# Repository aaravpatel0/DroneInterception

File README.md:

# DroneDetection

This is my drone tracking and turret project. The main goal was to detect a drone with a camera, estimate where it is in 3D space, and move a pan/tilt turret so the camera stays pointed at it.

I am Aarav Patel. I started this project as a computer vision turret, but it turned into a bigger system while I was building it. I worked on the YOLO detector, the live tracker, the Pico turret firmware, the CAD, and two custom PCBs. I also tried controlling a small commercial drone through its controller, but that got messy, so I moved toward custom electronics for the drone frame instead.

The project is not a finished product. It is a working prototype and a record of what I built, tested, changed, and still need to finish.

## Current Status

- The YOLOv8 drone detector works.
- The live camera tracker works.
- The tracker estimates the drone position relative to the camera.
- The tracker predicts short-term movement so the turret does not only react to the last frame.
- The Pico 2 turret controller moves pan with a stepper motor and tilt with a servo.
- Stepper acceleration ramping is in the firmware so the motor stalls less.
- The turret has been tested with live tracking and depth estimates.
- The drone PCB and turret PCB are designed and have fabrication files.
- The next hardware step is assembling and testing the manufactured boards.

## Project Photos

## Demo Links

| Demo | What it shows | Repo file | Drive link |
| --- | --- | --- | --- |
| YouTube project demo | Main video for the project | - | [Watch on YouTube](https://youtu.be/fUEFKIeKq6E?si=KoJLhP0QhyuUc3A9) |
| Live turret tracking | The physical turret tracking a detected drone | - | [Drone Tracking Turret.mp4](https://drive.google.com/file/d/1UBQOuaAiReNZodWpAV6A1nRXlFVHGqKZ/view?usp=drivesdk) |
| Detection proof of concept | Camera detection and tracking test | - | [Proof of Concept - Drone Tracked.mp4](https://drive.google.com/file/d/1Y8ixHSbWaxlFa2D4qZv8LF1yn2z77p-x/view?usp=drivesdk) |
| Fast follow simulation | Simulated drone following a target | [MP4](assets/demo_simulations/follow_tracking_demo.mp4) / [GIF](assets/demo_simulations/follow_tracking_demo.gif) | [Drive MP4](https://drive.google.com/file/d/1x22EfQROl3rcCMJz3o-rANU-yGck9Fjs/view?usp=drivesdk) / [Drive GIF](https://drive.google.com/file/d/1ceiqXWkpfdoIr6vI1aE4kro-Gwh2Y9jS/view?usp=drivesdk) |
| Orbit simulation | Simulated drone orbiting around the target | [MP4](assets/demo_simulations/orbit_tracking_demo.mp4) / [GIF](assets/demo_simulations/orbit_tracking_demo.gif) | [Drive MP4](https://drive.google.com/file/d/1vTIU1h2euXmmVWb8Ut7vwJZywcUVn1Vr/view?usp=drivesdk) / [Drive GIF](https://drive.google.com/file/d/1toew0ILT582uKQxMksciPWsyv_LBWJpW/view?usp=drivesdk) |
| Safe standoff simulation | Simulated follow behavior that keeps distance | [MP4](assets/demo_simulations/standoff_tracking_demo.mp4) / [GIF](assets/demo_simulations/standoff_tracking_demo.gif) | [Drive MP4](https://drive.google.com/file/d/1BEXhN5-Scd0X3nanZK4e2Cr_hdrNLuV4/view?usp=drivesdk) / [Drive GIF](https://drive.google.com/file/d/1r3fI6IdqFA_aWafnw3gRHlx3CpV9DbdE/view?usp=drivesdk) |
| Full ship folder | Videos, previews, and extra files | - | [Google Drive folder](https://drive.google.com/drive/folders/1Nn7UfG2TgwVNnhRaEpTsOkTEUmSowxKg) |

The simulation files are here:

- [drone_detector/live_tracker/demo_flight_simulations.ipynb](drone_detector/live_tracker/demo_flight_simulations.ipynb)
- [drone_detector/live_tracker/demo_flight_simulations.py](drone_detector/live_tracker/demo_flight_simulations.py)

To regenerate the simulation clips:

```powershell
cd C:\Users\aptcs\Downloads\Projects\DroneDetection
.\drone_detector\.venv\Scripts\python.exe .\drone_detector\live_tracker\demo_flight_simulations.py --scenario all
```

## CAD

I made the turret CAD in Onshape:

[Open the turret CAD in Onshape](https://cad.onshape.com/documents/1e954f2e6fb0afe0e50c1e47/w/2cc3740a39c70e9d1274ecfc/e/ad41d11dd19aaeac7b789fd0?renderMode=0&uiState=6a3ad88aa638e38f0ba9bea5)

## Project Layout

```text
DroneDetection/
|-- README.md
|-- JOURNAL.md
|-- assets/
|   |-- demo_simulations/          # rendered simulation videos and GIFs
|   `-- project_photos/            # photos, screenshots, and PCB previews
|-- Drone PCB/                     # drone-frame board KiCad files, Gerbers, and STEP
|-- Turret Control PCB/            # turret controller KiCad files, Gerbers, and STEP
|-- drone_detector/
|   |-- live_tracker/              # camera tracking, 3D position, prediction, turret control
|   |-- pico_turret_platformio/    # Pico 2 turret firmware
|   |-- pico_drone_platformio/     # Pico 2 drone-control firmware
|   |-- pico_drone_controller/     # older MicroPython drone-control prototype
|   |-- esp32_drone_bridge/        # ESP32-C3 and BMI160 test work
|   |-- scripts/                   # Docker and workflow helper scripts
|   |-- train_yolov8.py
|   |-- evaluate_model.py
|   `-- run_tracker_sim.ps1
|-- dataset_toolkit/               # dataset scripts and reports
`-- archived/                      # older files I kept for reference
```

## Hardware

### Turret

The turret uses:

- USB camera for video input.
- Raspberry Pi Pico 2 for the turret controller.
- Stepper driver and NEMA 17 stepper for pan.
- Servo for tilt.
- 12V input power.
- 12V-to-8.4V buck/BEC for the servo rail on the turret PCB.
- Custom turret controller PCB to replace the breadboard wiring.

### Drone Frame

I first tried controlling the drone by sending filtered voltage signals into the original controller. It kind of worked, but it was not clean enough. The original joystick circuit kept affecting the voltages, and I did not want the final version to depend on a hacked controller.

After that, I designed a custom board for the small SP350-style drone frame. The board is meant to reuse the frame, motors, and propellers, but make the electronics easier to understand and modify.

The drone PCB includes:

- A compact shape for the reused frame.
- Four brushed motor outputs.
- Pads for motor and battery wires.
- Shared ground and cleaner power routing.
- Space to keep working on offboard control electronics.

## How It Works

### 1. Dataset And Training

I used YOLO-format drone datasets and merged them into one dataset with one class: `drone`. The scripts can merge datasets, clean labels, preview annotations, train the model, and evaluate it.

Main scripts:

- `drone_detector/merge_roboflow_datasets.py`
- `drone_detector/clean_dataset.py`
- `drone_detector/preview_labels.py`
- `drone_detector/train_yolov8.py`
- `drone_detector/evaluate_model.py`

The tracker looks for this model first:

```text
drone_detector/models/production_drone_model.pt
```

If it is not there, it tries this one:

```text
drone_detector/models/drone_roboflow_best.pt
```

### 2. Detection

`drone_detector/live_tracker/turret_tracker.py` reads camera frames and runs YOLOv8. It picks the best drone box, finds the center of that box, and compares it to the center of the camera frame.

```text
error_x = box_center_x - frame_center_x
error_y = box_center_y - frame_center_y
```

That error becomes the basic pan and tilt correction.

### 3. 3D Position Estimate

The camera is treated like the origin:

```text
camera = (0.0, 0.0, 0.0) inches
```

The tracker estimates:

```text
x = left/right from the camera center
y = up/down from the camera center
z = forward distance away from the camera
```

Depth comes from the visible width of the drone in the camera image. The code uses the camera focal length, the expected drone width, and the bounding-box width to estimate distance. Then it uses the camera angle to turn that into `x`, `y`, and `z`.

### 4. Prediction

The raw position jumps around because camera detections are noisy. I added filtering so one bad frame does not make the turret move too much.

The prediction code:

- Smooths the measured position.
- Smooths velocity.
- Softens unrealistic jumps.
- Predicts a small amount into the future.
- Limits the prediction arrow length.

Current launcher defaults:

```text
prediction horizon: 0.18 seconds
max prediction step: 14 inches
position smoothing alpha: 0.55
velocity smoothing alpha: 0.30
lost target hold: 0.15 seconds
```

### 5. Pan And Tilt

The Python tracker sends simple USB serial commands to the Pico:

```text
PAN <steps>
TILT <angle>
PANZERO
STATUS
STOP
```

Pan uses the horizontal pixel error. Tilt uses the vertical estimate and stays inside the servo limits. If the target disappears for a short moment, the turret holds the last filtered position instead of instantly snapping somewhere else.

### 6. Stepper Ramp

The Pico firmware ramps the stepper speed at the start and end of a move:

```text
slow start pulse delay -> fast cruise pulse delay -> slow ending pulse delay
```

This helped because the stepper was more likely to stall when it started too fast.

## Quick Start

Run the tracker:

```powershell
cd C:\Users\aptcs\Downloads\Projects\DroneDetection\drone_detector
.\.venv\Scripts\Activate.ps1
.\run_tracker_sim.ps1 -Port COM6 -Source 0
```

Use a lower pan gain if the turret overshoots:

```powershell
.\run_tracker_sim.ps1 -Port COM6 -Source 0 -KpPan 0.40
```

Emergency stop:

```powershell
.\.venv\Scripts\python.exe -c "import serial,time; s=serial.Serial('COM6',115200,timeout=1); time.sleep(1); s.write(b'K\n'); s.flush(); time.sleep(.3); print(s.read(200).decode(errors='ignore').strip()); s.close()"
```

Check Pico status:

```powershell
.\.venv\Scripts\python.exe -c "import serial,time; s=serial.Serial('COM6',115200,timeout=1); time.sleep(1); s.write(b'STATUS\n'); s.flush(); time.sleep(.3); print(s.read(300).decode(errors='ignore').strip()); s.close()"
```

## Upload Pico Turret Firmware

```powershell
cd C:\Users\aptcs\Downloads\Projects\DroneDetection\drone_detector\pico_turret_platformio
..\.venv\Scripts\python.exe -m platformio run -e rpipico2 --target upload
```

## Training Workflow

Put Roboflow YOLOv8 exports here:

```text
drone_detector/data/roboflow_raw/Drone1
drone_detector/data/roboflow_raw/Drone2
drone_detector/data/roboflow_raw/Drone3
```

Run the local workflow:

```powershell
cd C:\Users\aptcs\Downloads\Projects\DroneDetection\drone_detector
python preflight_check.py --fix-dirs
python preflight_check.py
python merge_roboflow_datasets.py
python clean_dataset.py
python preview_labels.py --split train --count 20
python preflight_check.py --smoke-train
```

Train and evaluate:

```powershell
python train_yolov8.py --device auto
python evaluate_model.py --device auto
```

## PCB Files

Both PCB folders include the KiCad project files, Gerbers/drill files, DRC reports, board previews, fabrication ZIPs, and STEP files.

| Board | Fabrication package | STEP file | Preview | Drive links |
| --- | --- | --- | --- | --- |
| SP350 drone-frame PCB | [SP350_PCB_fabrication.zip](Drone%20PCB/SP350_PCB_fabrication.zip) | [Drone PCB.step](Drone%20PCB/Drone%20PCB.step) | [sp350_fc_compact.svg](Drone%20PCB/preview/sp350_fc_compact.svg) | [Gerbers](https://drive.google.com/file/d/1_clK4amSKWlXcbOoY3qKn666rn6Dt4GA/view?usp=drivesdk) / [Preview](https://drive.google.com/file/d/1AM0e_IHqhc1ucxpBFDUrG8czhq44fBtK/view?usp=drivesdk) |
| Turret controller PCB | [Turret_Control_PCB_fabrication.zip](Turret%20Control%20PCB/Turret_Control_PCB_fabrication.zip) | [Turret Control PCB.step](Turret%20Control%20PCB/Turret%20Control%20PCB.step) | [turret_control.svg](Turret%20Control%20PCB/preview/turret_control.svg) | [Gerbers](https://drive.google.com/file/d/1bgDib1TZAem1N0iuNZMGmwHZ0CROYYnE/view?usp=drivesdk) / [Preview](https://drive.google.com/file/d/17CKoOh3Z418mv7G7dEkDwoyh0OWlZMZ4/view?usp=drivesdk) |

The current DRC reports show `0 DRC violations` and `0 unconnected pads` for both boards.

## Debugging And Tuning

The tracker prints lines like this while it runs:

```text
[track] DETECT conf=0.82 err=(+74,-12) x=+8.4in y=+1.2in z=42.0in target_x=+8.4in target_y=+1.2in -> pico2 PAN +37 TILT 86
```

Things I tuned while testing:

- Increase `KpPan` if pan is too slow.
- Decrease `KpPan` if the turret overshoots.
- Increase `deadband-x` if it jitters near the center.
- Decrease `imgsz` for lower latency.
- Increase `imgsz` if detections are unreliable.
- Increase stepper current carefully if the motor stalls under load.
- Increase the slow pulse delay in firmware if the stepper needs an easier start.

## Credits

I designed, assembled, tested, and debugged this project. I also made the turret CAD.

The drone-frame prototype reuses the original Snaptain SP350-style frame, brushed motors, and propellers. Snaptain gets credit for those original commercial drone parts.

I used outside resources while learning about drone controls, PCB design, and simulation work, but the project idea, physical testing, wiring, debugging decisions, dataset work, CAD, and final integration choices are mine.

## Safety

This project is for controlled tracking and electronics testing. When changing firmware, wiring, or control logic, test with the propellers removed or with the drone restrained.

## More Documentation

- [JOURNAL.md](JOURNAL.md): build journal and project timeline.
- [drone_detector/README.md](drone_detector/README.md): training and detector details.
- [drone_detector/live_tracker/README.md](drone_detector/live_tracker/README.md): live tracker notes.
- [drone_detector/pico_turret_platformio/README.md](drone_detector/pico_turret_platformio/README.md): Pico turret firmware.
- [drone_detector/pico_drone_platformio/README.md](drone_detector/pico_drone_platformio/README.md): Pico drone controller firmware.
- [dataset_toolkit/README.md](dataset_toolkit/README.md): dataset tooling.

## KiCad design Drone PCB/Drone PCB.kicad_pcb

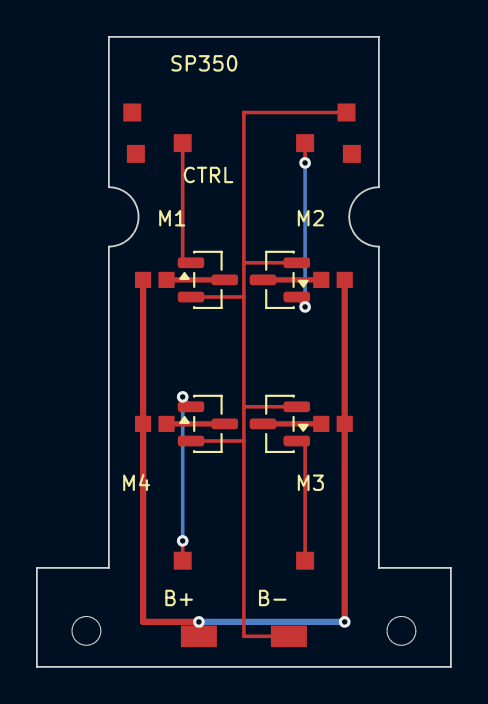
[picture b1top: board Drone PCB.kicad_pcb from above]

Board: 2 copper layers, 23.0 x 35.0 mm, 24 parts (0 on the bottom side), 10 nets.

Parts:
B+: VBAT
B-: GND
H1, H2: NPTH
M1+, M2+, M3+, M4+: VBAT
M1-: M1_LOW
M2-: M2_LOW
M3-: M3_LOW
M4-: M4_LOW
P1: 3V3
P2: GND
P3: M1PWM
P4: M2PWM
P5: M3PWM
P6: M4PWM
P7: SDA
P8: SCL
Q1: M1; SOT-23
Q2: M2; SOT-23
Q3: M3; SOT-23
Q4: M4; SOT-23

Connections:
GND: B-.1, P2.1, Q1.2, Q2.2, Q3.2, Q4.2
M1_LOW: M1-.1, Q1.3
M1_PWM: P3.1, Q1.1
M2_LOW: M2-.1, Q2.3
M2_PWM: P4.1, Q2.1
M3_LOW: M3-.1, Q3.3
M3_PWM: P5.1, Q3.1
M4_LOW: M4-.1, Q4.3
M4_PWM: P6.1, Q4.1
VBAT: B+.1, M1+.1, M2+.1, M3+.1, M4+.1

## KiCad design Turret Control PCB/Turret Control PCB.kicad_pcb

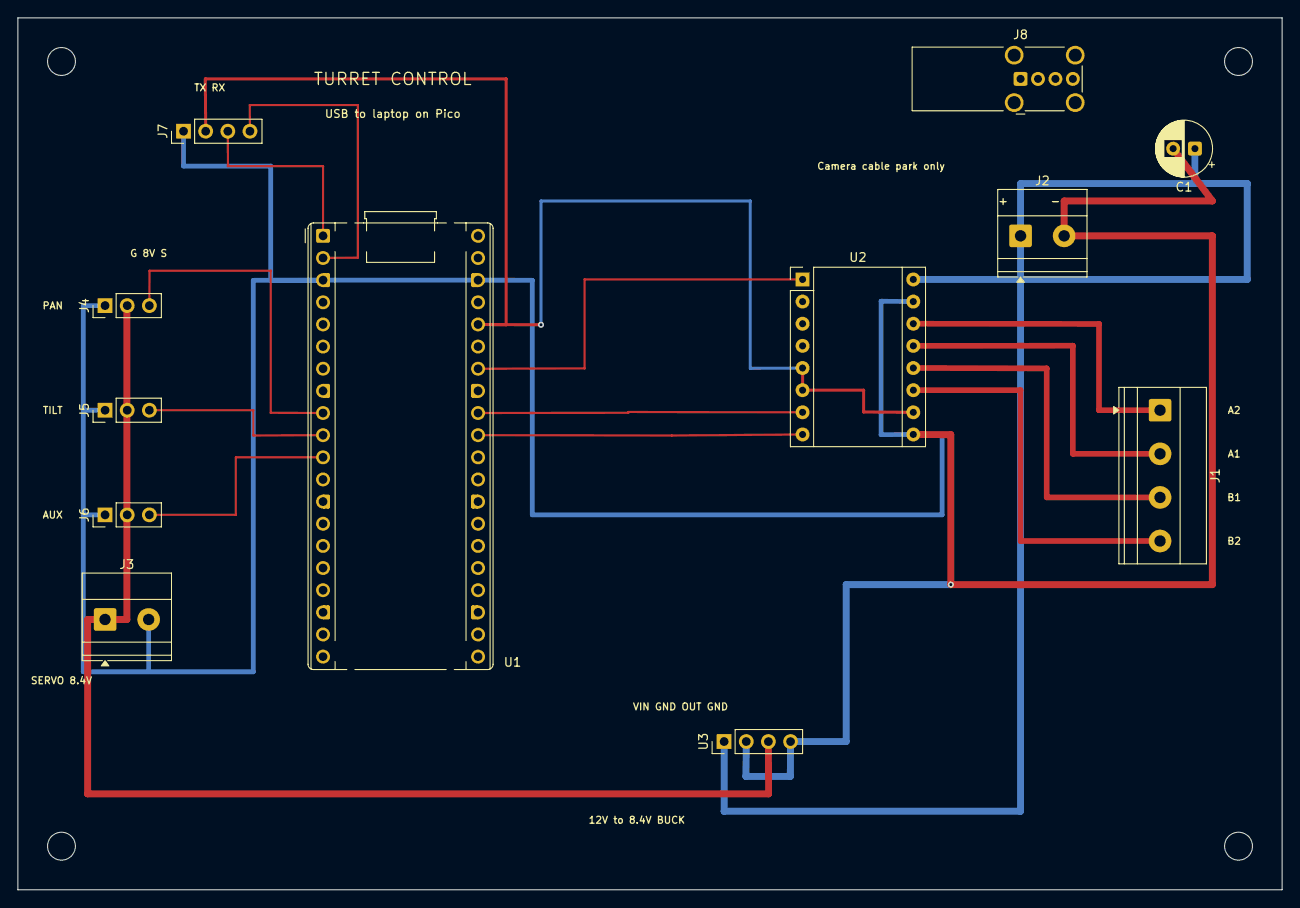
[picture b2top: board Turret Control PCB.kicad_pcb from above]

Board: 2 copper layers, 145.0 x 100.0 mm, 16 parts (0 on the bottom side), 16 nets.

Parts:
C1: 100uF VMOT; CP_Radial_D6.3mm_P2.50mm
H1, H2, H3, H4: M3
J1: STEPPER; TerminalBlock_Phoenix_MKDS-1,5-4_1x04_P5.00mm_Horizontal
J2: VMOT IN; TerminalBlock_Phoenix_MKDS-1,5-2_1x02_P5.00mm_Horizontal
J3: SERVO 8.4V OUT; TerminalBlock_Phoenix_MKDS-1,5-2_1x02_P5.00mm_Horizontal
J4: J4; PinHeader_1x03_P2.54mm_Vertical
J5: J5; PinHeader_1x03_P2.54mm_Vertical
J6: J6; PinHeader_1x03_P2.54mm_Vertical
J7: DRONE UART; PinHeader_1x04_P2.54mm_Vertical
J8: USB CAMERA PARK; USB_A_Wuerth_614004134726_Horizontal
U1: Pico/Pico 2; RaspberryPi_Pico_Common_THT
U2: A4988/DRV8825; Pololu_Breakout-16_15.2x20.3mm
U3: 12V->8.4V BUCK; PinHeader_1x04_P2.54mm_Vertical

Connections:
3V3: J7.2, U1.36, U2.5, U2.6, U2.10
DIR: U1.31, U2.8
EN: U1.34, U2.1
GND: C1.2, J2.2, J3.2, J4.1, J5.1, J6.1, J7.1, U1.3, U1.38, U2.9, U2.15, U3.2, U3.4
MOT_A1: J1.2, U2.13
MOT_A2: J1.1, U2.14
MOT_B1: J1.3, U2.12
MOT_B2: J1.4, U2.11
SERVO_AUX: J6.3, U1.11
SERVO_PAN: J4.3, U1.9
SERVO_TILT: J5.3, U1.10
STEP: U1.32, U2.7
UART_RX: J7.4, U1.2
UART_TX: J7.3, U1.1
VMOT: C1.1, J2.1, U2.16, U3.1
VSERVO: J3.1, J4.2, J5.2, J6.2, U3.3

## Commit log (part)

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2026-06-23 Prepare project release
2026-06-23 Update CAD link
2026-06-27 Add project journal
2026-06-27 Revise project journal
2026-06-27 Add project demo link
2026-06-28 Add images to README and journal
2026-06-28 adding final iamges
2026-06-29 add pcb steps
